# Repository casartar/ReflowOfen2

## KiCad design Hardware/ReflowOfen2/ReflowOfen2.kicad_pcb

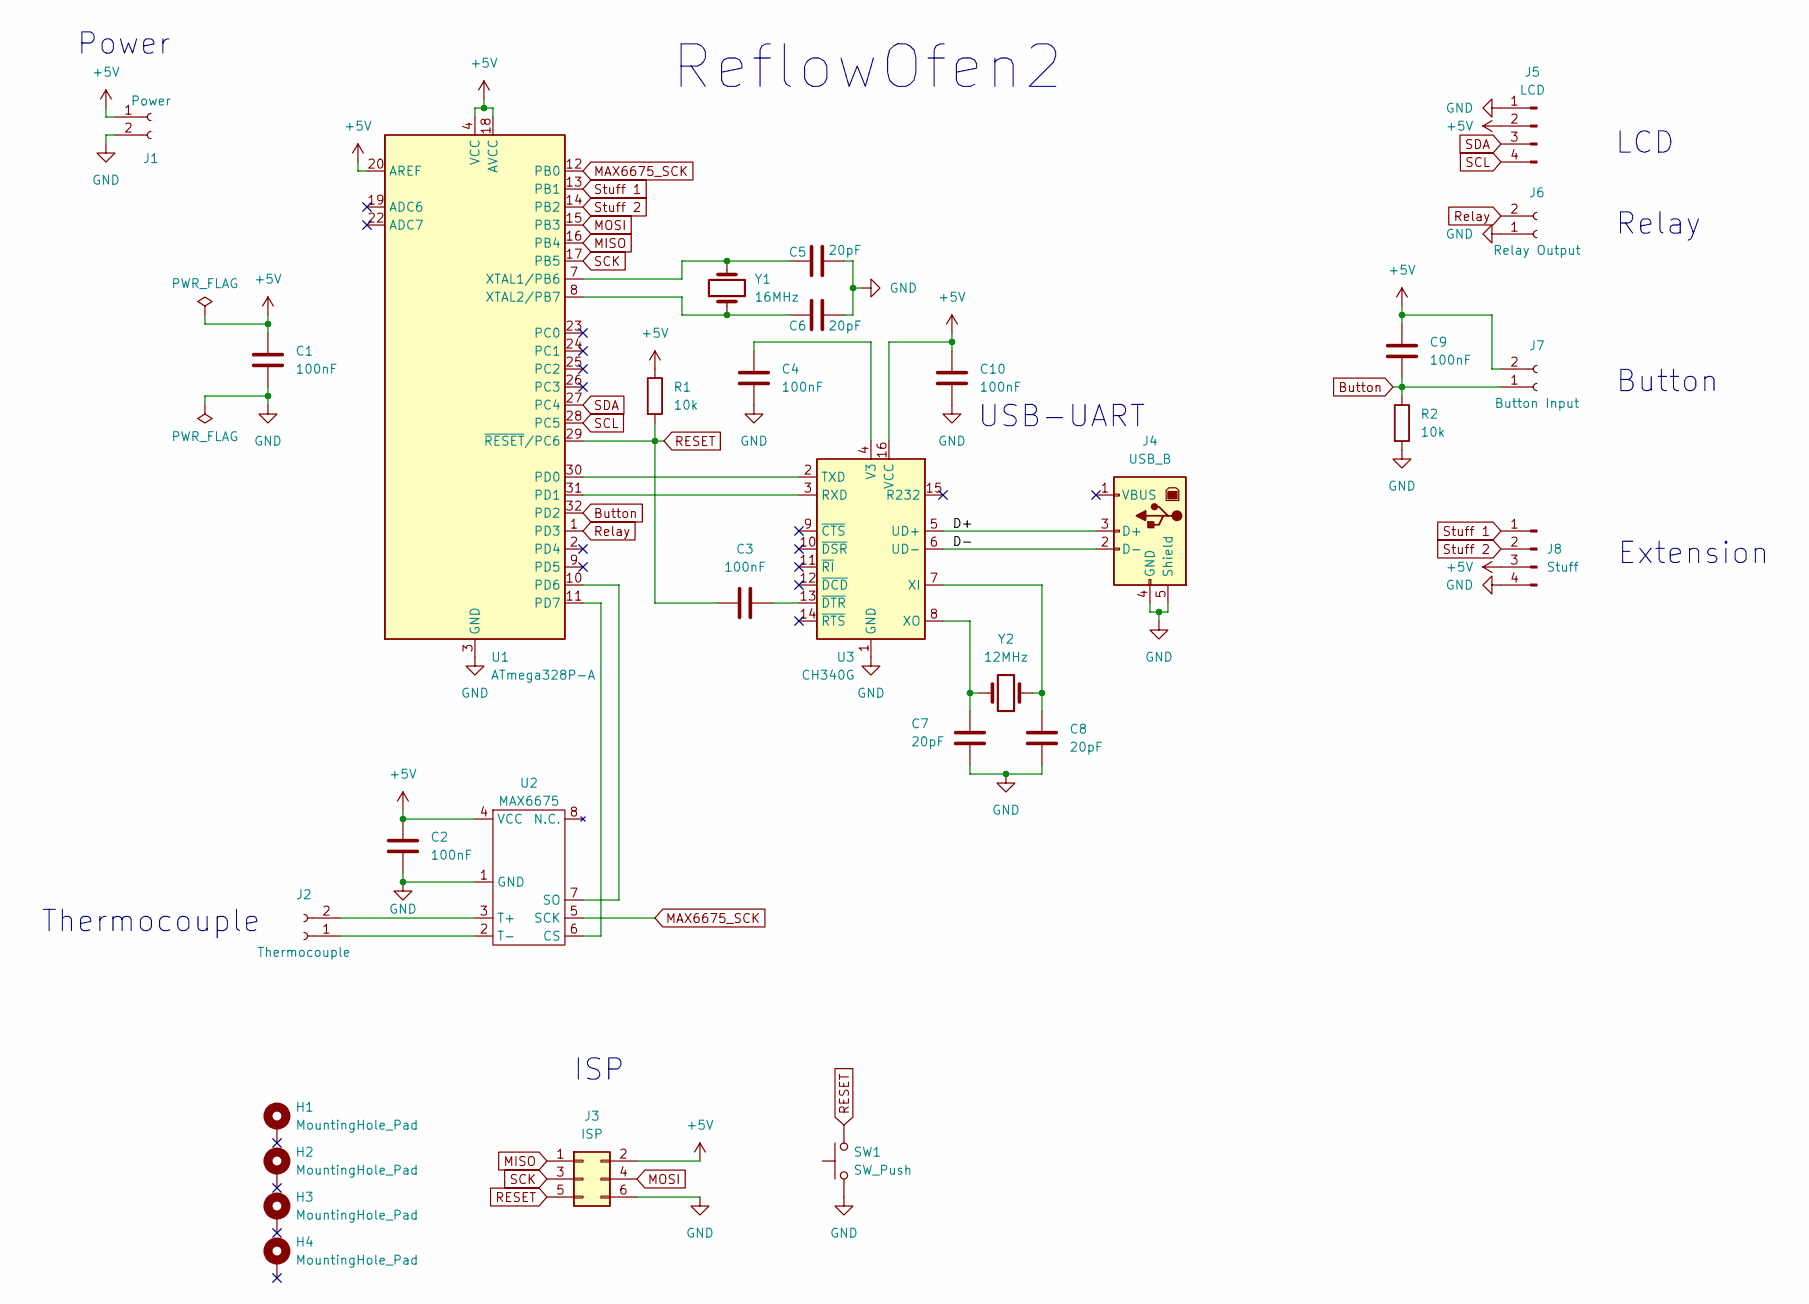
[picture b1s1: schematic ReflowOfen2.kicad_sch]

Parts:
C1, C2, C3, C4, C9, C10: 100nF; C_0805_2012Metric
C5, C6, C7, C8: 20pF; C_0805_2012Metric
H1, H2, H3, H4: MountingHole_Pad; MountingHole_3.2mm_M3_DIN965_Pad
J1: Power; TerminalBlock_bornier-2_P5.08mm
J2: Thermocouple; TerminalBlock_bornier-2_P5.08mm
J3: ISP; PinHeader_2x03_P2.54mm_Vertical
J4: USB_B; USB_B_Lumberg_2411_02_Horizontal
J5: LCD; PinHeader_1x04_P2.54mm_Vertical
J6: Relay Output; TerminalBlock_bornier-2_P5.08mm
J7: Button Input; TerminalBlock_bornier-2_P5.08mm
J8: Stuff; PinHeader_1x04_P2.54mm_Vertical
R1, R2: 10k; R_0805_2012Metric
SW1: SW_Push; SW_PUSH_6mm
U1: ATmega328P-A; TQFP-32_7x7mm_P0.8mm
U2: MAX6675; SOIC-8_3.9x4.9mm_P1.27mm
U3: CH340G; SOIC-16_3.9x9.9mm_P1.27mm
Y1: 16MHz; Crystal_HC51-U_Vertical
Y2: 12MHz; Crystal_HC51-U_Vertical

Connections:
+5V: C1.1, C2.1, C9.1, C10.1, J1.1, J3.2, J5.2, J7.2, J8.3, R1.1, U1.4 (VCC), U1.6 (VCC), U1.18 (AVCC), U1.20 (AREF), U2.4 (VCC), U3.16 (VCC)
/D+: J4.3 (D+), U3.5 (UD+)
/D-: J4.2 (D-), U3.6 (UD-)
Button: C9.2, J7.1, R2.1, U1.32 (PD2)
GND: C1.2, C2.2, C4.2, C5.2, C6.2, C7.1, C8.1, C10.2, J1.2, J3.6, J4.4 (GND), J4.5 (Shield), J5.1, J6.1, J8.4, R2.2, SW1.1, U1.3 (GND), U1.5 (GND), U1.21 (GND), U2.1 (GND), U3.1 (GND)
MAX6675_SCK: U1.12 (PB0), U2.5 (SCK)
MISO: J3.1, U1.16 (PB4)
MOSI: J3.4, U1.15 (PB3)
unnamed: J2.1, U2.2 (T-)
unnamed: J2.2, U2.3 (T+)
unnamed: U1.30 (PD0), U3.2 (TXD)
unnamed: U1.31 (PD1), U3.3 (RXD)
unnamed: U1.10 (PD6), U2.7 (SO)
unnamed: U1.11 (PD7), U2.6 (CS)
unnamed: C5.1, U1.7 (XTAL1/PB6), Y1.2
unnamed: C6.1, U1.8 (XTAL2/PB7), Y1.1
unnamed: C4.1, U3.4 (V3)
unnamed: C8.2, U3.7 (XI), Y2.1
unnamed: C7.2, U3.8 (XO), Y2.2
unnamed: C3.2, U3.13 (~DTR)
RESET: C3.1, J3.5, R1.2, SW1.2, U1.29 (~RESET/PC6)
Relay: J6.2, U1.1 (PD3)
SCK: J3.3, U1.17 (PB5)
SCL: J5.4, U1.28 (PC5)
SDA: J5.3, U1.27 (PC4)
Stuff 1: J8.1, U1.13 (PB1)
Stuff 2: J8.2, U1.14 (PB2)

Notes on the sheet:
Thermocouple
ISP
Relay
Button
USB-UART
Power
LCD
Extension
ReflowOfen2

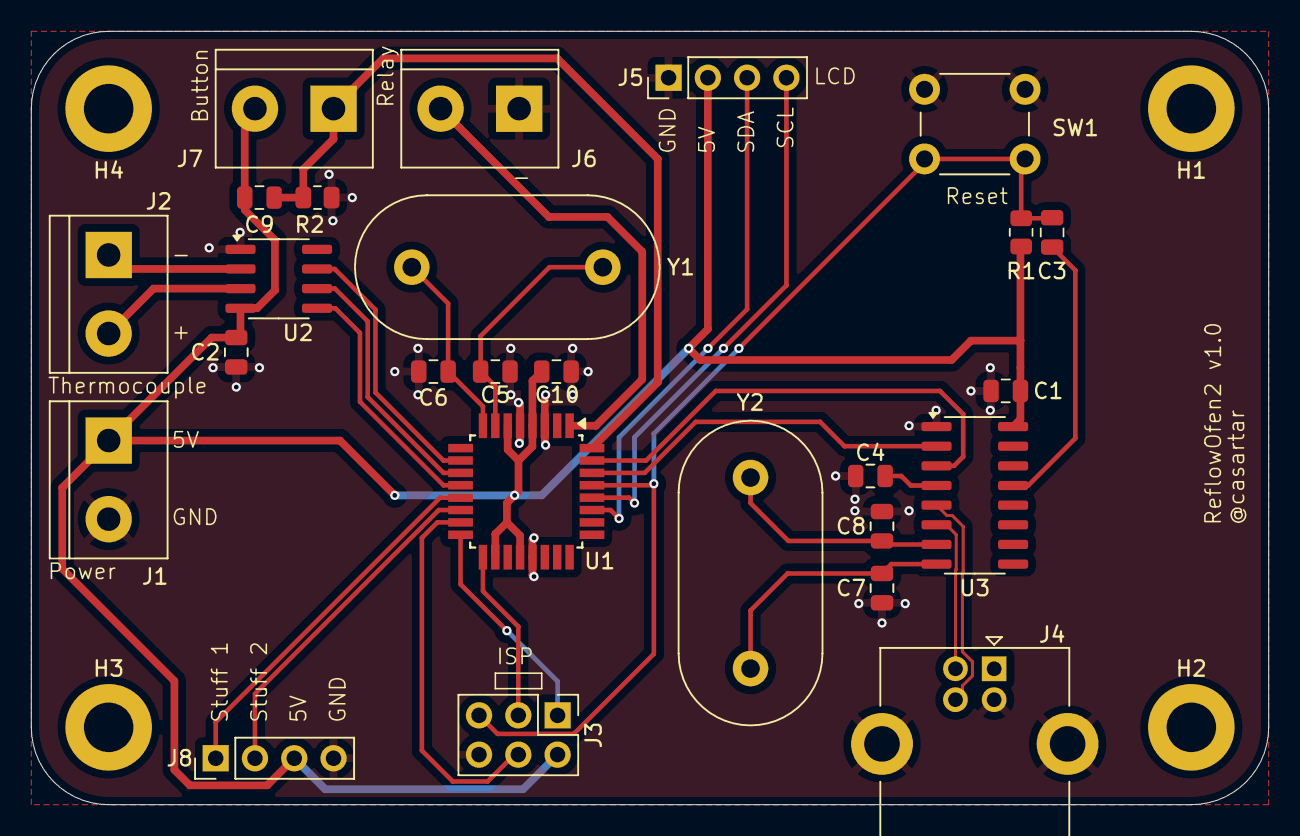
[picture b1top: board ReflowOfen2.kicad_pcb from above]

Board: 2 copper layers, 80.0 x 50.0 mm, 30 parts (0 on the bottom side), 27 nets.
